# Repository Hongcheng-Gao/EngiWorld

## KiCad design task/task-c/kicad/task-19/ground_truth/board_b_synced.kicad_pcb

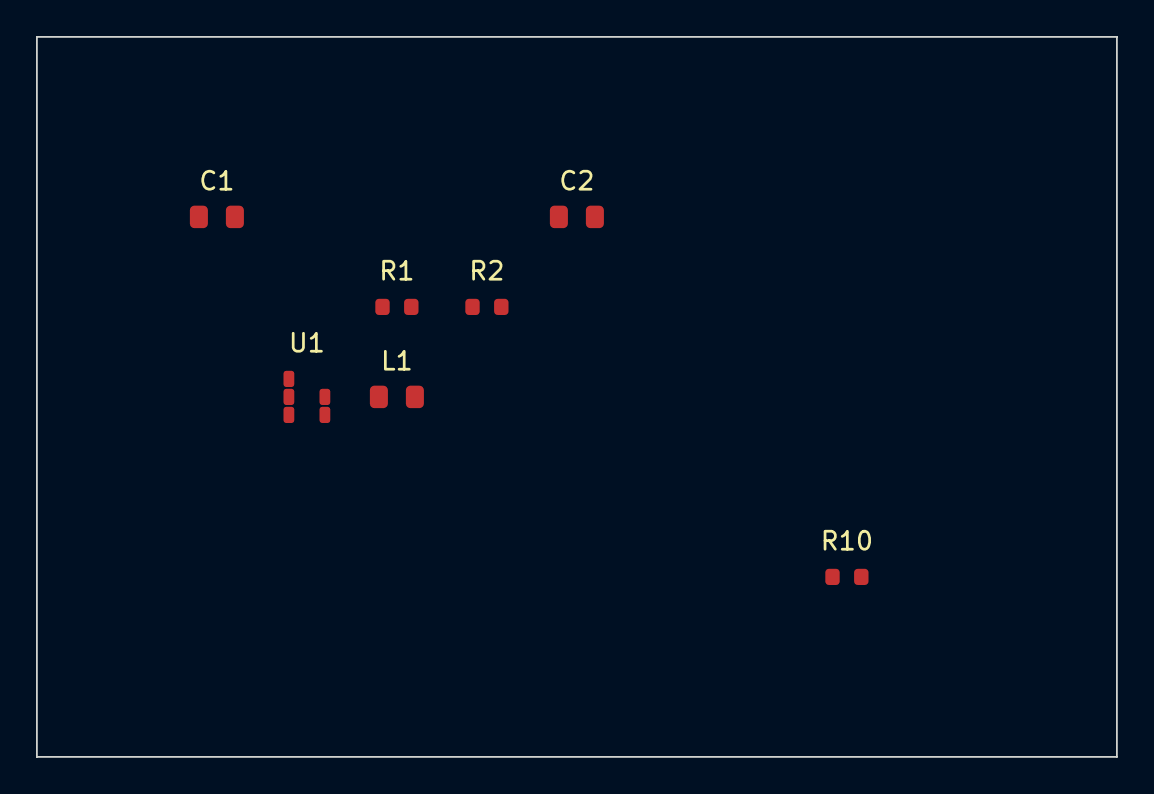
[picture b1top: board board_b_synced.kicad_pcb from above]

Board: 2 copper layers, 60.0 x 40.0 mm, 7 parts (0 on the bottom side), 5 nets, no tracks yet.

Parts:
C1: 10uF; C_0805
C2: 22uF; C_0805
L1: 4u7; L_0805
R1: 10k; R_0603
R2: 2k2; R_0603
R10: 1k; R_0603
U1: LM3671; SOT-23-5

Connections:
FB: R1.2, R2.1, U1.4
GND: C1.2, C2.2, R2.2, R10.2, U1.2
SW: L1.1, U1.1
VIN: C1.1, U1.3, U1.5
VOUT: C2.1, L1.2, R1.1, R10.1

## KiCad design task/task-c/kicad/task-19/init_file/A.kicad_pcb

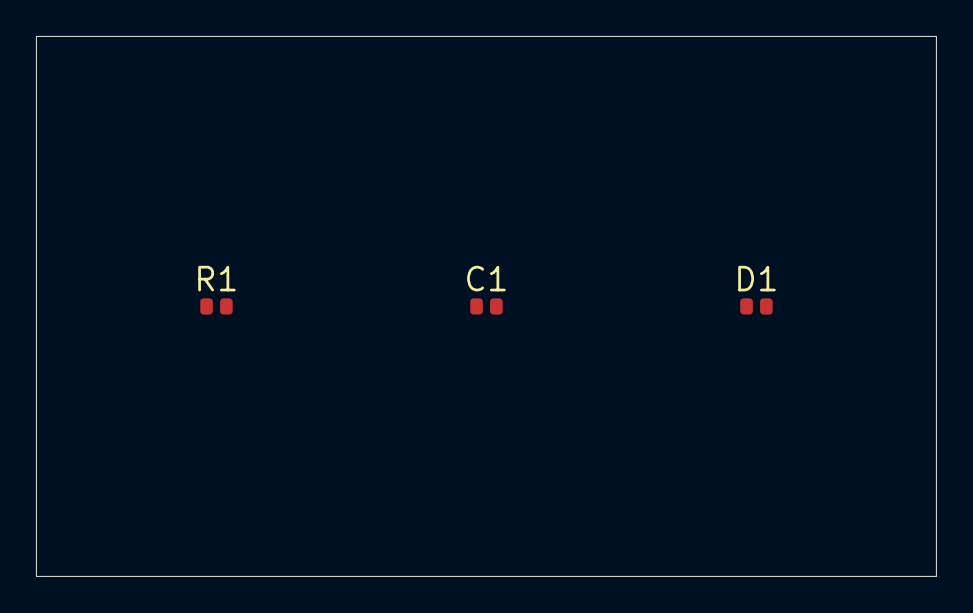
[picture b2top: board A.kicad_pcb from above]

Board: 2 copper layers, 50.0 x 30.0 mm, 3 parts (0 on the bottom side), 3 nets, no tracks yet.

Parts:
C1: 100nF; C_0402
D1: LED_G; LED_0402
R1: 10k; R_0402

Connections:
GND: C1.2, D1.2
SIG: D1.1, R1.2
VCC: C1.1, R1.1

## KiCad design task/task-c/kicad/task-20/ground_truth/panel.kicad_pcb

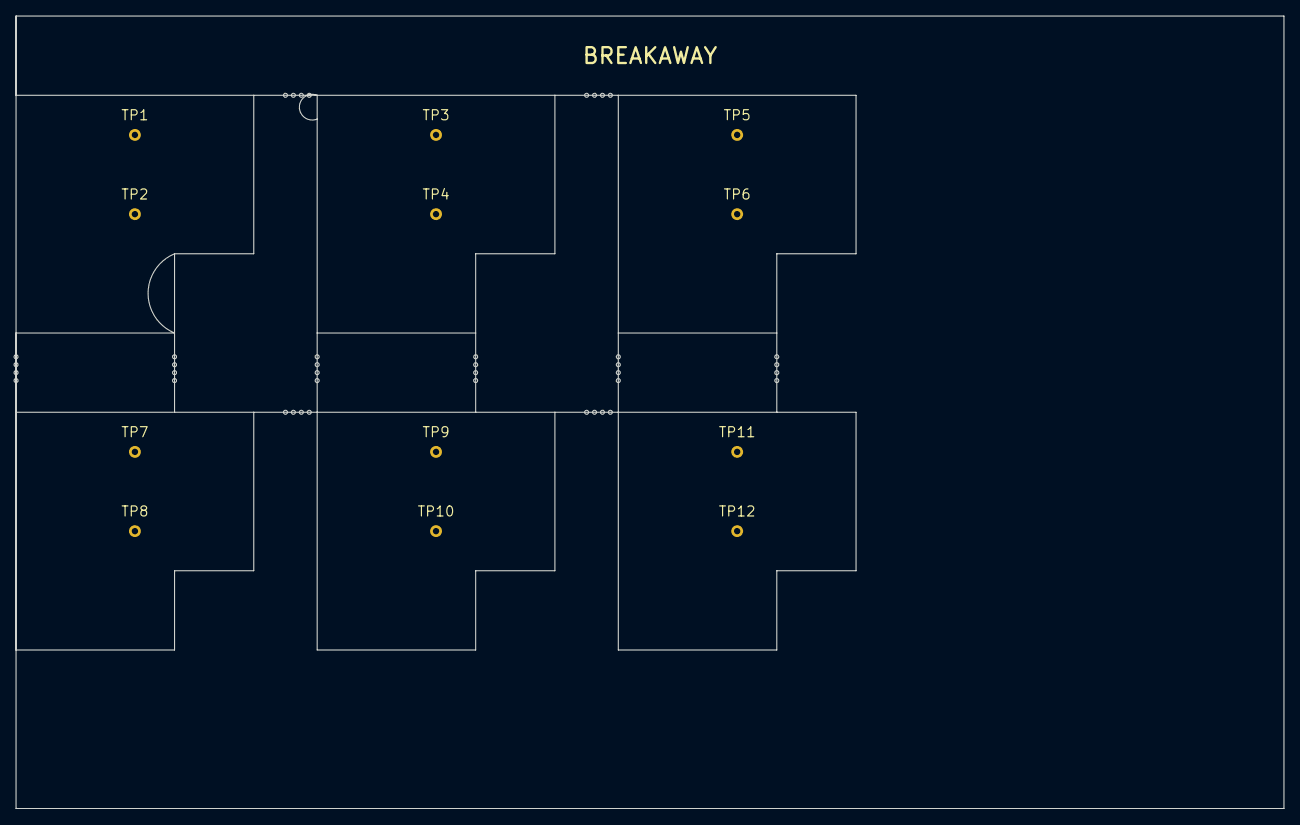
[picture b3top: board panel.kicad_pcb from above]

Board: 2 copper layers, 160.0 x 100.0 mm, 13 parts (0 on the bottom side), 2 nets, no tracks yet.

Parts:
MB1: MouseBiteArray
TP1, TP2, TP3, TP4, TP5, TP6, TP7, TP8, TP9, TP10, TP11, TP12: TP; TestPoint_Pad_D1.5mm

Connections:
GND: TP2.1, TP4.1, TP6.1, TP8.1, TP10.1, TP12.1
VCC: TP1.1, TP3.1, TP5.1, TP7.1, TP9.1, TP11.1

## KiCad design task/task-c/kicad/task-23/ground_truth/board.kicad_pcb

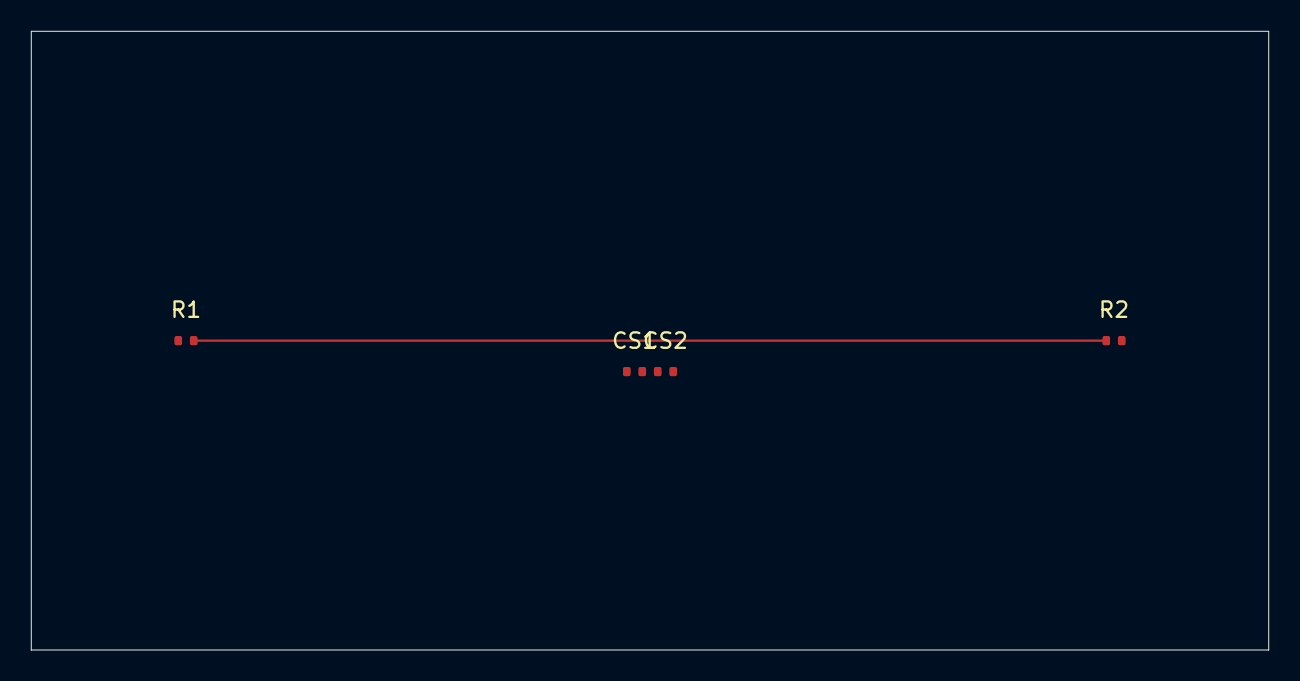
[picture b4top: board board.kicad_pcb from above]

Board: 4 copper layers, 80.0 x 40.0 mm, 4 parts (0 on the bottom side), 4 nets.

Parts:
CS1, CS2: 100n; C_0402
R1, R2: 100; R_0402

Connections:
+3V3: CS1.2, CS2.2
GND: CS1.1, CS2.1
HS1: R1.1, R1.2
HS2: R2.1, R2.2
